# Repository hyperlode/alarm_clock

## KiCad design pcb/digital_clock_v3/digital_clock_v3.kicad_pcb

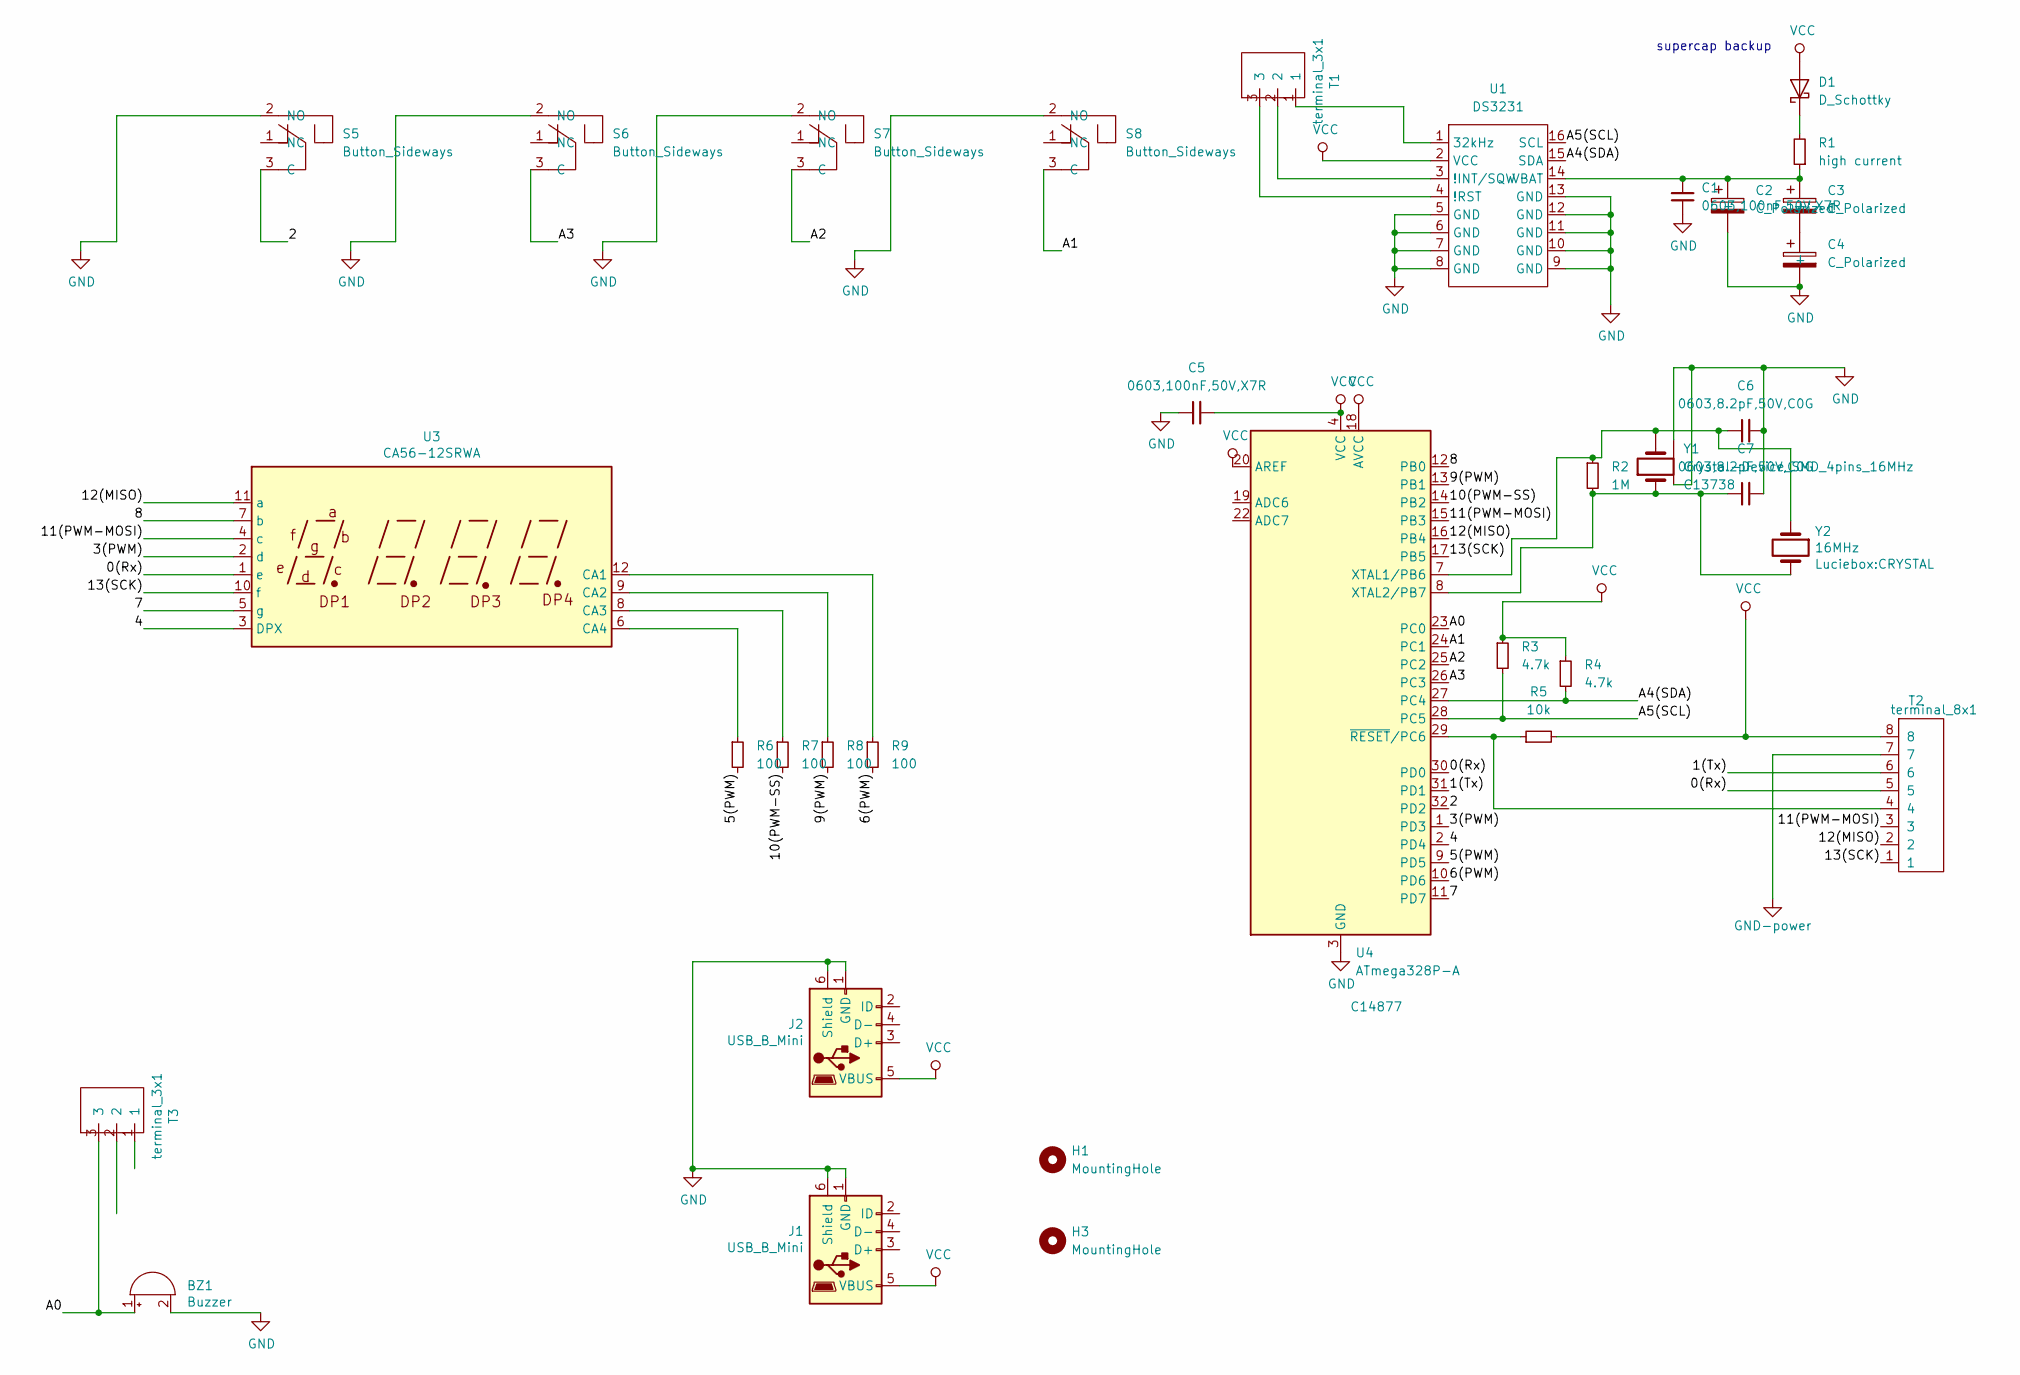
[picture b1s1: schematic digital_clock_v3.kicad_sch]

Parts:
BZ1: Buzzer; buzzer
C1, C5: 0603,100nF,50V,X7R; C_0603_1608Metric; MFGPN CC0603KRX7R9BB104; LCSC C14663
C2, C3, C4: C_Polarized; polarized_capacitor
C6, C7: 0603,8.2pF,50V,C0G; C_0603_1608Metric; MFGPN 0603CG8R2C500NT; LCSC C1685
D1: D_Schottky; smd_throughhole_2_pins
H1, H3: MountingHole; MountingHole_4.3mm_M4
J1, J2: USB_B_Mini; usb_mini_Molex-0548190519
R1: high current; R_0603_1608Metric; MFGPN 0603WAF1004T5E; LCSC C22935
R2: 1M; R_0603_1608Metric; MFGPN 0603WAF1004T5E; LCSC C22935
R3, R4: 4.7k; R_0603_1608Metric; MFGPN 0603WAF4701T5E; LCSC C23162
R5: 10k; R_0603_1608Metric; MFGPN 0603WAF1002T5E; LCSC C25804
R6, R7, R8, R9: 100; R_0402_1005Metric; MFGPN 0402WGF1000TCE; LCSC C25076
S5, S6, S7, S8: Button_Sideways; Button_LAZ16-11_sideways; MPN KS-01Q-01; Digi-Key_PN EG4791-ND
T1, T3: terminal_3x1; Terminal_3x1_100mil
T2: terminal_8x1; Terminal_8x1_100mil
U1: DS3231; SOIC-16W_7.5x10.3mm_P1.27mm
U3: CA56-12SRWA
U4: ATmega328P-A; TQFP-32_7x7mm_P0.8mm; LCSC C14877
Y1: Crystal-Device_SMD_4pins_16MHz; Crystal_SMD_3225-4Pin_3.2x2.5mm; JLCS C13738
Y2: 16MHz; CRYSTAL

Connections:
/0(Rx): T2.5, U3.1 (e), U4.30 (PD0)
/1(Tx): T2.6, U4.31 (PD1)
/2: S5.3 (C), U4.32 (PD2)
/3(PWM): U3.2 (d), U4.1 (PD3)
/4: U3.3 (DPX), U4.2 (PD4)
/5(PWM): R6.2, U4.9 (PD5)
/6(PWM): R9.2, U4.10 (PD6)
/7: U3.5 (g), U4.11 (PD7)
/8: U3.7 (b), U4.12 (PB0)
/9(PWM): R8.2, U4.13 (PB1)
/10(PWM-SS): R7.2, U4.14 (PB2)
/11(PWM-MOSI): T2.3, U3.4 (c), U4.15 (PB3)
/12(MISO): T2.2, U3.11 (a), U4.16 (PB4)
/13(SCK): T2.1, U3.10 (f), U4.17 (PB5)
/A0: BZ1.1 (-), T3.3, U4.23 (PC0)
/A1: S8.3 (C), U4.24 (PC1)
/A2: S7.3 (C), U4.25 (PC2)
/A3: S6.3 (C), U4.26 (PC3)
/A4(SDA): R4.2, U1.15 (SDA), U4.27 (PC4)
/A5(SCL): R3.2, U1.16 (SCL), U4.28 (PC5)
unnamed: C1.2, C2.1 (+), C3.1 (+), R1.1, U1.14 (VBAT)
unnamed: C3.2 (-), C4.1 (+)
unnamed: C6.1, R2.1, U4.7 (XTAL1/PB6), Y1.3 (OSC2), Y2.1
unnamed: C7.1, R2.2, U4.8 (XTAL2/PB7), Y1.1 (OSC1), Y2.2
unnamed: D1.1 (K), R1.2
unnamed: R5.1, T2.4, U4.29 (~RESET/PC6)
unnamed: R6.1, U3.6 (CA4)
unnamed: R7.1, U3.8 (CA3)
unnamed: R8.1, U3.9 (CA2)
unnamed: R9.1, U3.12 (CA1)
unnamed: T1.1, U1.1 (32kHz)
unnamed: T1.2, U1.3 (!INT/SQW)
unnamed: T1.3, U1.4 (!RST)
VCC: C5.2, D1.2 (A), J1.5 (VBUS), J2.5 (VBUS), R3.1, R4.1, R5.2, T2.8, U1.2 (VCC), U4.4 (VCC), U4.6 (VCC), U4.18 (AVCC), U4.20 (AREF)

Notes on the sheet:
supercap backup

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
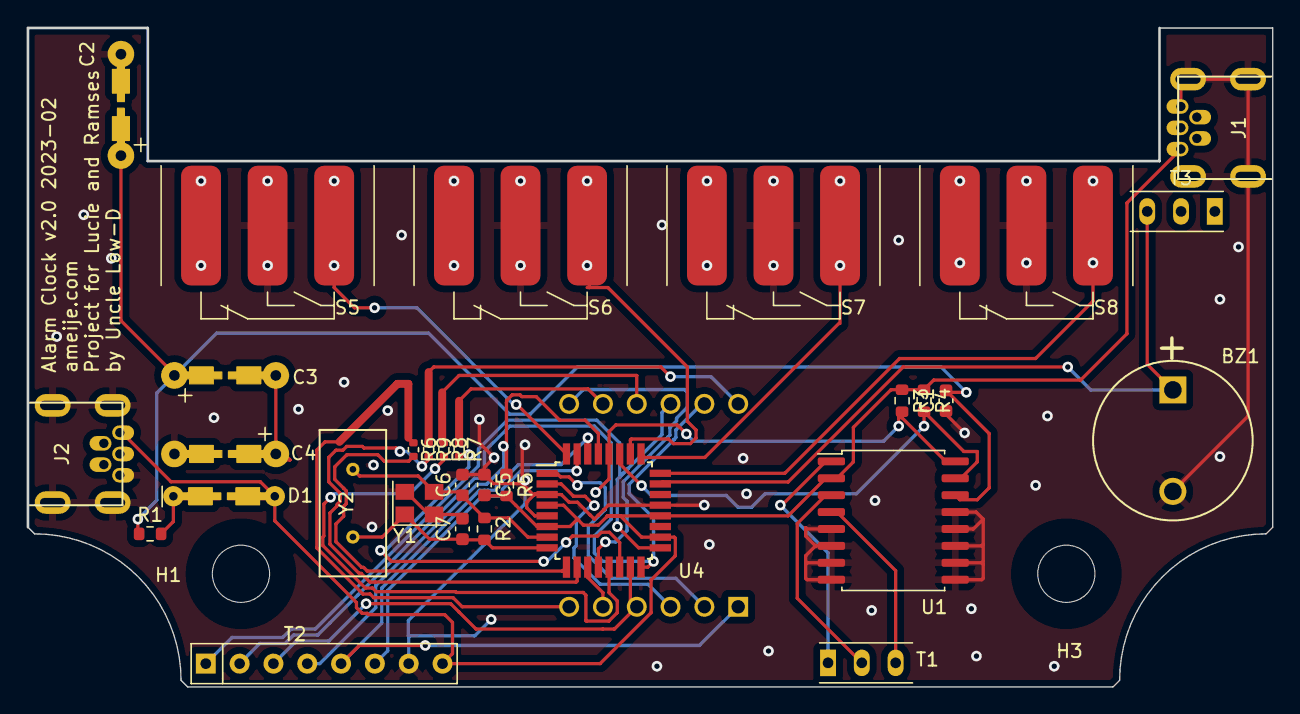
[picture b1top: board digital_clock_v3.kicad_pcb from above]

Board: 2 copper layers, 93.5 x 49.4 mm, 34 parts (1 on the bottom side), 35 nets.

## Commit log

2022-09-04 Clock demo working and added a button
2022-09-04 Button as separate class
2022-09-04 Use momentary button as toggle button
2022-09-04 Add 7 segment display SMA410561KX
2022-09-05 Make display dimmable with pwm
2022-09-05 reorganize file structure
2022-09-05 Brightness through lookup table
2022-09-06 Add two more buttons, three in total
2022-09-06 Set up state machine
2022-09-06 Refactor to functions
2022-09-06 Reduce flicker with delay
2022-09-07 Modify hour
2022-09-07 full time modification
2022-09-07 Cleanup
2022-09-07 Enable dark night mode
2022-09-07 Dark mode bugfix
2022-09-07 midnight minutes display bugfix
2022-09-09 display time immediatley after quiting dark mode
2022-09-09 minutes and seconds display mode ahead of time setting
2022-09-09 Alarm menu stable but unfinished
2022-09-09 Set and adjust alarm time. No buzzer yet
2022-09-09 Blink resistant value changing during time setting
2022-09-09 Implement buzzer, but tone at line114 of buzzer.cpp is giving trouble (try it in dimmed mode) things crash.
2022-09-11 PWM no interference with tone. Swapped pins. Sound test
2022-09-11 Auto time out alarm menu
2022-09-11 Alarm clock functioning (alarm time not retentive at power off)
2022-09-11 bugfix crash at serial.println during alarm AT time setting
2022-09-14 Bugfix vibrating minutes:seconds display
2022-09-14 rtc memory readout (doesn't really seem to work), update display timeouts
2022-09-14 Alarm settings save in eeprom
2022-09-20 Add mirrored clock idea
2022-09-20 Bugfix alarm set dot display after dark mode
2022-09-21 Add extra button
2022-09-23 Start adding kitchen timer, debug serial
2022-09-23 Auto Format .ino
2022-09-23 Continue work on kitchentimer
2022-09-23 Change name of main state
2022-09-23 optimize kitchen timer
2022-09-24 Kitchen timer improvement
2022-09-24 Display minutes:seconds blinking colon
2022-09-24 Change alarm enable toggle button
2022-09-25 Save kitchen timer state to eeprom
2022-09-25 Kitchen timer reset bugfix
2022-09-26 Enable long pressing buttons
2022-09-26 Kitchen timer blink settings
2022-09-26 Fine tune display dot
2022-09-26 Adjust setting values and blinking behaviour
2022-09-30 Set alarm with long press
2022-10-10 Long press for timer. long press period setting
2022-10-13 Snooze indicator dot behaviour bugfix
2022-10-13 Main layout
2022-10-14 Rework button positions
2022-10-14 main menu titles set up
2022-10-14 Layout
2022-10-14 Configure eeprom, factory settings at first startup. Set snooze time
2022-10-14 Hourly beep functionality
2022-10-15 Set time through menu
2022-10-15 various little changes
2022-10-15 Bugfix long press button behaviour
2022-10-15 Swap button positions
2022-10-15 Simplify alarm
2022-10-15 Alarm status and snooze status saved in eeprom. You know, for pre flight sleep power cuts!
2022-10-15 Buttons change function when alarm triggers (they become snooze buttons)
2022-10-16 Implement decreasing snooze time'
2022-10-17 Decreasing snooze bug fix
2022-10-17 Bugfix change time while kitchen timer running
2022-10-20 Add pcb schematic and start of layout
2022-10-23 Add pcb design, not yet ready
2022-10-28 Bugfix alarm sounds. Play alarm sounds in menu
2022-10-28 Menu UI improvements
2022-10-30 Add incremental alarm tune
2022-10-31 flickering at low brightness middle digits at colon blink
2022-11-01 Brightness, ditch PWM. Stable, but bad with dimming of course
2022-11-14 PCB Send out v1
2022-11-21 Ditch PWM for multiplexing. Change multiplex to per digit instead of per segment. Good results
2022-12-03 Swap pins for the v1 pcb
2022-12-03 Kitchen timer save to eeprom at timer start
2022-12-04 Integrate the DS3231
2022-12-04 eeprom write routine
2022-12-04 Change main menu controls slightly
2022-12-09 Disable serial
2023-02-06 v2 pcb create. No traces yet.
2023-02-06 Finish v2 pcb wiring
2023-02-06 Correct button positions
2023-02-16 Add v2 pcb. Code clean up
2023-02-17 Brightness control depending of amount of segments set in a digit
2023-02-17 Flicker reduction complete
2023-02-18 Set brightness. Nice and smooth. Maybe still a tad too bright
2023-02-18 Set brightness levels. Fix instant start/stop bug at longpress for kitchentimer
2023-02-20 Display indictor dot during dark mode
2023-02-20 Bugfix dark mode
2023-02-20 Protection against millis rollover
2023-02-20 Add more millis rollover protection
2023-02-20 Fix more millis rollover bugs
2023-02-20 Formatting
2023-02-21 Bugfix long press not smooth for kitchen timer
2023-02-21 Clean up
2023-03-02 Fix bug: unsigned long casting
2023-03-02 Add enable rtc chip menu
2023-03-22 RTC on/off works well
2023-04-18 pcb and enclosure
2023-04-18 Alarm minutes settable without crashing. Bug not reproducable after reuploading...
2023-06-19 Improve kitchen timer behaviour. Long press time extend
2023-07-28 Create v3 pcb
